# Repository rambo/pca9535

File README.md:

# PCA9535 library

Used to control this I2C I/O expander

Note: default device addresses etc suppose that the adress lines are *pulled up* when not explicitly set, this is what the breakout board (pca9535bo.brd) does by default (user can then pull them down via solder jumpers)

The device has no internal pull-ups that could be enabled (bit of a shame for input purposes...) so I also made a "wing" board with pull-ups and also series resistors for driving LEDs (pca9535bowing.brd)

## Installing

Clone this repo to your arduino libraries folder, then clone the following repos as well

  * git://github.com/rambo/I2C.git
  * git://github.com/rambo/i2c_device.git

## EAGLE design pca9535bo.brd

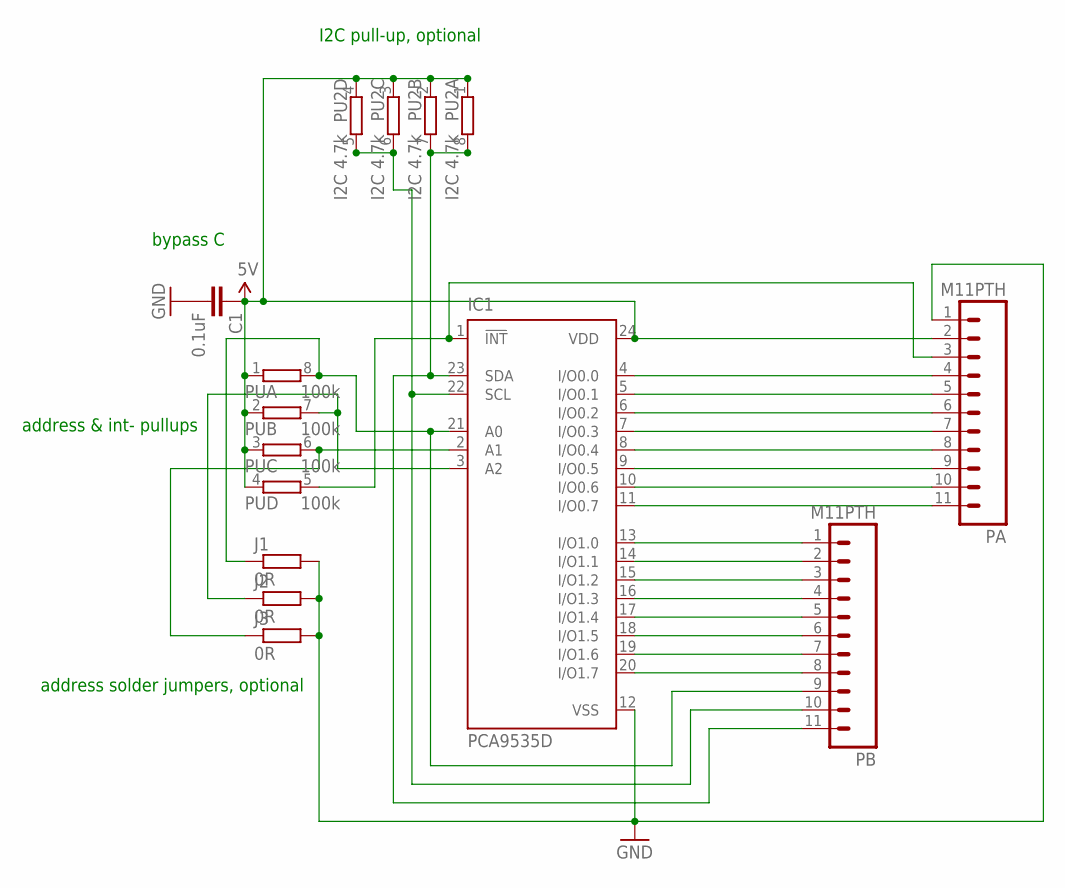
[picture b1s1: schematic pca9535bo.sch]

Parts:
C1: 0.1uF; C0805K
IC1: PCA9535D; SO24
J1, J2, J3: 0R; R0603
PA: M11PTH; 1X11
PB: M11PTH; 1X11
PU: 100k; CAY16
PU2: I2C 4.7k; CAY16

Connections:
5V: C1.1, IC1.24 (VDD), PA.2, PU.1, PU.2 (1), PU.3 (1), PU.4 (1), PU2.1, PU2.2 (1), PU2.3 (1), PU2.4 (1)
A0: IC1.21 (A0), J1.1, PB.9, PU.8 (2)
A1: IC1.2 (A1), J3.1, PU.6 (2)
A2: IC1.3 (A2), J2.1, PU.7 (2)
GND: C1.2, IC1.12 (VSS), J1.2, J2.2, J3.2, PA.1
INT-: IC1.1 (!INT), PA.3, PU.5 (2)
PA0: IC1.4 (I/O0.0), PA.4
PA1: IC1.5 (I/O0.1), PA.5
PA2: IC1.6 (I/O0.2), PA.6
PA3: IC1.7 (I/O0.3), PA.7
PA4: IC1.8 (I/O0.4), PA.8
PA5: IC1.9 (I/O0.5), PA.9
PA6: IC1.10 (I/O0.6), PA.10
PA7: IC1.11 (I/O0.7), PA.11
PB0: IC1.13 (I/O1.0), PB.1
PB1: IC1.14 (I/O1.1), PB.2
PB2: IC1.15 (I/O1.2), PB.3
PB3: IC1.16 (I/O1.3), PB.4
PB4: IC1.17 (I/O1.4), PB.5
PB5: IC1.18 (I/O1.5), PB.6
PB6: IC1.19 (I/O1.6), PB.7
PB7: IC1.20 (I/O1.7), PB.8
SCL: IC1.22 (SCL), PB.10, PU2.5 (2), PU2.6 (2)
SDA: IC1.23 (SDA), PB.11, PU2.7 (2), PU2.8 (2)

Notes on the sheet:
I2C pull-up, optional
address solder jumpers, optional
address & int- pullups
bypass C

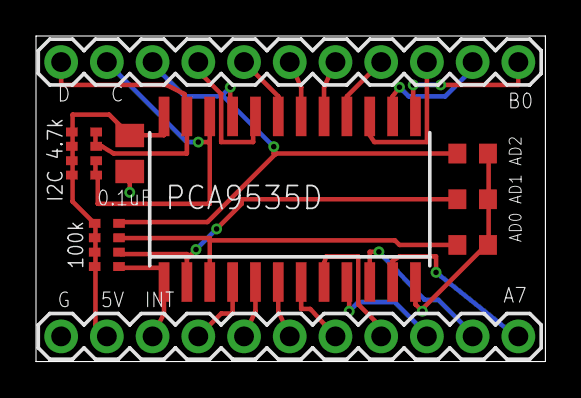
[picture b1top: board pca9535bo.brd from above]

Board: 2 copper layers, 28.3 x 18.1 mm, 9 parts (0 on the bottom side), 24 nets.

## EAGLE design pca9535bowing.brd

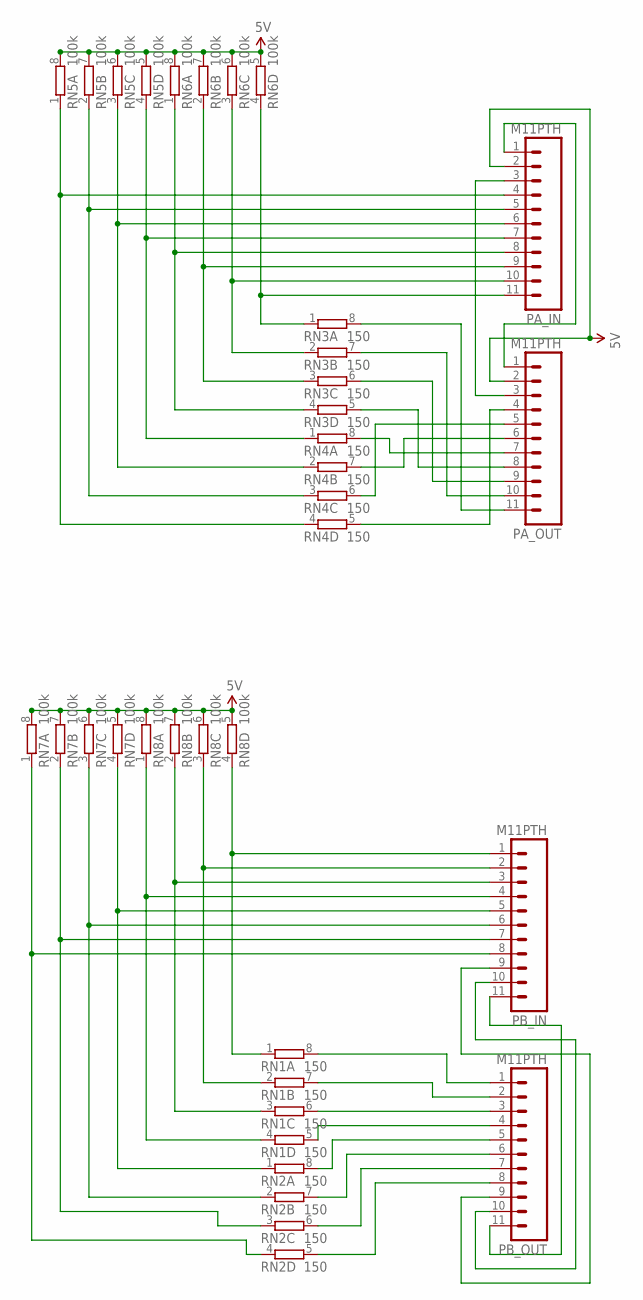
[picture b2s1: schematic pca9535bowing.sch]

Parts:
PA_IN: M11PTH; 1X11
PA_OUT: M11PTH; 1X11
PB_IN: M11PTH; 1X11
PB_OUT: M11PTH; 1X11
RN1, RN2, RN3, RN4: 150; CAY16
RN5, RN6, RN7, RN8: 100k; CAY16

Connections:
5V: PA_IN.2, PA_OUT.2, RN5.5 (2), RN5.6 (2), RN5.7 (2), RN5.8 (2), RN6.5 (2), RN6.6 (2), RN6.7 (2), RN6.8 (2), RN7.5 (2), RN7.6 (2), RN7.7 (2), RN7.8 (2), RN8.5 (2), RN8.6 (2), RN8.7 (2), RN8.8 (2)
unnamed: PB_IN.1, RN1.1, RN8.4 (1)
unnamed: PB_IN.2, RN1.2 (1), RN8.3 (1)
unnamed: PB_IN.3, RN1.3 (1), RN8.2 (1)
unnamed: PB_IN.4, RN1.4 (1), RN8.1
unnamed: PB_IN.5, RN2.1, RN7.4 (1)
unnamed: PB_IN.6, RN2.2 (1), RN7.3 (1)
unnamed: PB_IN.7, RN2.3 (1), RN7.2 (1)
unnamed: PB_IN.8, RN2.4 (1), RN7.1
unnamed: PA_IN.11, RN3.1, RN6.4 (1)
unnamed: PA_IN.10, RN3.2 (1), RN6.3 (1)
unnamed: PA_IN.9, RN3.3 (1), RN6.2 (1)
unnamed: PA_IN.8, RN3.4 (1), RN6.1
unnamed: PA_IN.7, RN4.1, RN5.4 (1)
unnamed: PA_IN.6, RN4.2 (1), RN5.3 (1)
unnamed: PA_IN.5, RN4.3 (1), RN5.2 (1)
unnamed: PA_IN.4, RN4.4 (1), RN5.1
unnamed: PA_IN.1, PA_OUT.1
unnamed: PA_IN.3, PA_OUT.3
unnamed: PA_OUT.4, RN4.5 (2)
unnamed: PA_OUT.5, RN4.6 (2)
unnamed: PA_OUT.6, RN4.7 (2)
unnamed: PA_OUT.7, RN4.8 (2)
unnamed: PA_OUT.8, RN3.5 (2)
unnamed: PA_OUT.9, RN3.6 (2)
unnamed: PA_OUT.10, RN3.7 (2)
unnamed: PA_OUT.11, RN3.8 (2)
unnamed: PB_IN.11, PB_OUT.11
unnamed: PB_IN.10, PB_OUT.10
unnamed: PB_IN.9, PB_OUT.9
unnamed: PB_OUT.1, RN1.8 (2)
unnamed: PB_OUT.2, RN1.7 (2)
unnamed: PB_OUT.3, RN1.6 (2)
unnamed: PB_OUT.4, RN1.5 (2)
unnamed: PB_OUT.5, RN2.8 (2)
unnamed: PB_OUT.6, RN2.7 (2)
unnamed: PB_OUT.7, RN2.6 (2)
unnamed: PB_OUT.8, RN2.5 (2)

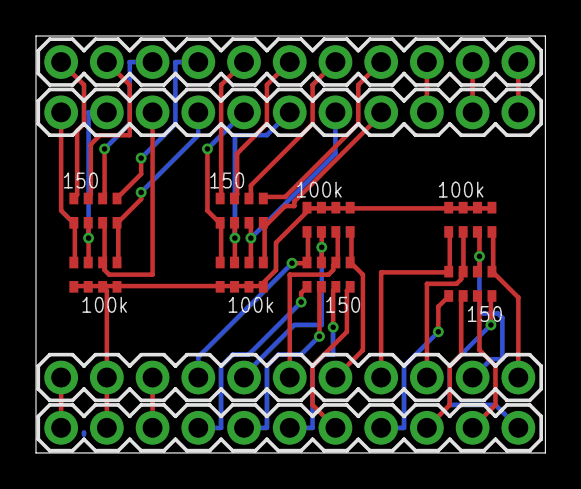
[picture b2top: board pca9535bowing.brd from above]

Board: 2 copper layers, 28.3 x 23.2 mm, 12 parts (0 on the bottom side), 38 nets.

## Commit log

2012-04-26 the breakout board, moved here from the hacklab reactor project
2012-04-26 stub class
2012-04-26 readme
2012-04-26 datasheet for reference
2012-04-26 stub example
2012-04-26 fix copy-paste issue
2012-04-26 correct address and some usefull debugs
2012-04-26 implement the basic functionality (NOTE: not actually tested, only compiled...)
2012-04-26 implementing some usefull methods
2012-04-26 use the previously defined port_read_modify_write for digitalWrite
2012-04-26 this should cover the features of the chip in both easy and efficient approaches
2012-04-26 example for using interrupt to read the data, though it seems this is a very bad idea if you have floating pins...
2012-04-26 added a TODO
2012-04-26 clarified the ASCII graphic
2012-04-29 started working on the "wing" to handle pull-ups etc
2012-04-29 adjust fonts, removed unneccessary part identifiers
2012-04-29 first layout
2012-04-29 forgot to connect the pull-ups to voltage...
2012-04-29 autorouted
2012-04-29 the values need to be moved to the names layer to be seen...
2012-04-30 the wingboard is done (and first prototype batch ordered from Seeedstudio), also other clarifications
2012-04-30 tested the interrupt handling, added some comments and usefull status reporting
2012-04-30 one more note about floating pins
2012-04-30 nicer approach to the floating pins problem
2012-04-30 trying to extend the bounce library to be used with the expander
2012-04-30 ended up having to cpoy instead of extending the class due to the constructor madness used in the original library
2012-04-30 rebounce included to example
2012-04-30 return correct value just in case someone expects it to be actually exact match
2012-04-30 support for more sane reading of multiple input pins
2012-04-30 added note about to origins
2012-04-30 calculate device address based on board number (which is inverted BCD for the 3 address bits [that are pulled UP by default])
2012-08-13 switch to flash strings: gsed -i -r -e "s%Serial.print(ln)?\\((\".*?\")\\)%Serial.print\1(F(\2))%g"

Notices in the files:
parts and their libraries:
SparkFun: Licensing: CC v3.0 Share-Alike You are welcome to use this library for commercial purposes.
